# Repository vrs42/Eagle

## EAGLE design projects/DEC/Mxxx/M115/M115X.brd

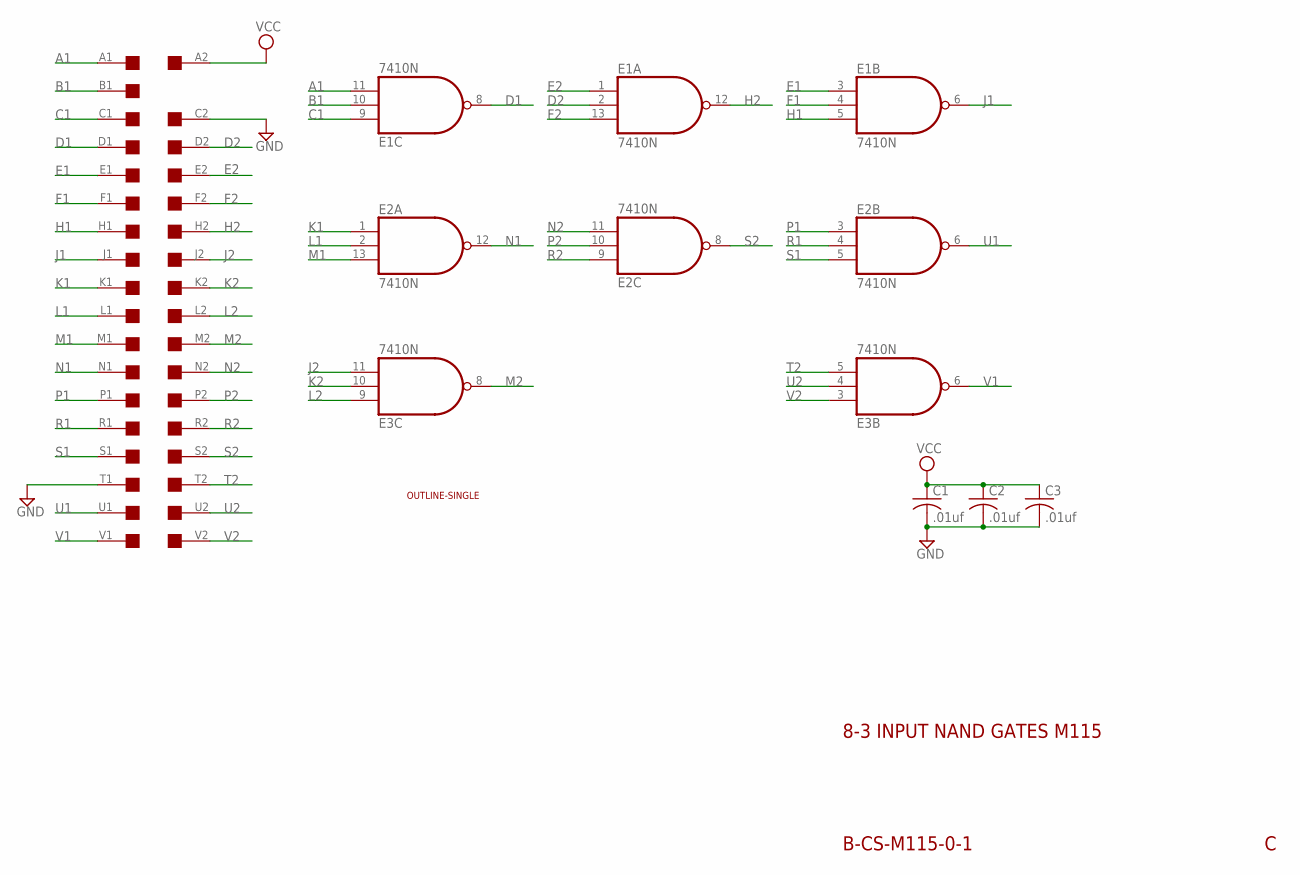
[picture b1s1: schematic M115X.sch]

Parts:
C1, C2, C3: .01uf; C050-025X075
E1, E2, E3: 7410N; DIL14
U$1: SINGLE; EDGE-CON2
U$4: OUTLINE-SINGLE; SINGLE

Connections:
A1: E1.11 (I2), U$1.A1
B1: E1.10 (I1), U$1.B1
C1: E1.9 (I0), U$1.C1
D1: E1.8 (O), U$1.D1
D2: E1.2 (I1), U$1.D2
E1: E1.3 (I0), U$1.E1
E2: E1.1 (I0), U$1.E2
F1: E1.4 (I1), U$1.F1
F2: E1.13 (I2), U$1.F2
GND: C1.2, C2.2, C3.2, E1.7 (GND), E2.7 (GND), E3.7 (GND), U$1.C2, U$1.T1
H1: E1.5 (I2), U$1.H1
H2: E1.12 (O), U$1.H2
J1: E1.6 (O), U$1.J1
J2: E3.11 (I2), U$1.J2
K1: E2.1 (I0), U$1.K1
K2: E3.10 (I1), U$1.K2
L1: E2.2 (I1), U$1.L1
L2: E3.9 (I0), U$1.L2
M1: E2.13 (I2), U$1.M1
M2: E3.8 (O), U$1.M2
N1: E2.12 (O), U$1.N1
N2: E2.11 (I2), U$1.N2
P1: E2.3 (I0), U$1.P1
P2: E2.10 (I1), U$1.P2
R1: E2.4 (I1), U$1.R1
R2: E2.9 (I0), U$1.R2
S1: E2.5 (I2), U$1.S1
S2: E2.8 (O), U$1.S2
T2: E3.5 (I2), U$1.T2
U1: E2.6 (O), U$1.U1
U2: E3.4 (I1), U$1.U2
V1: E3.6 (O), U$1.V1
V2: E3.3 (I0), U$1.V2
VCC: C1.1, C2.1, C3.1, E1.14 (VCC), E2.14 (VCC), E3.14 (VCC), U$1.A2

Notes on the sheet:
8-3 INPUT NAND GATES M115
B-CS-M115-0-1

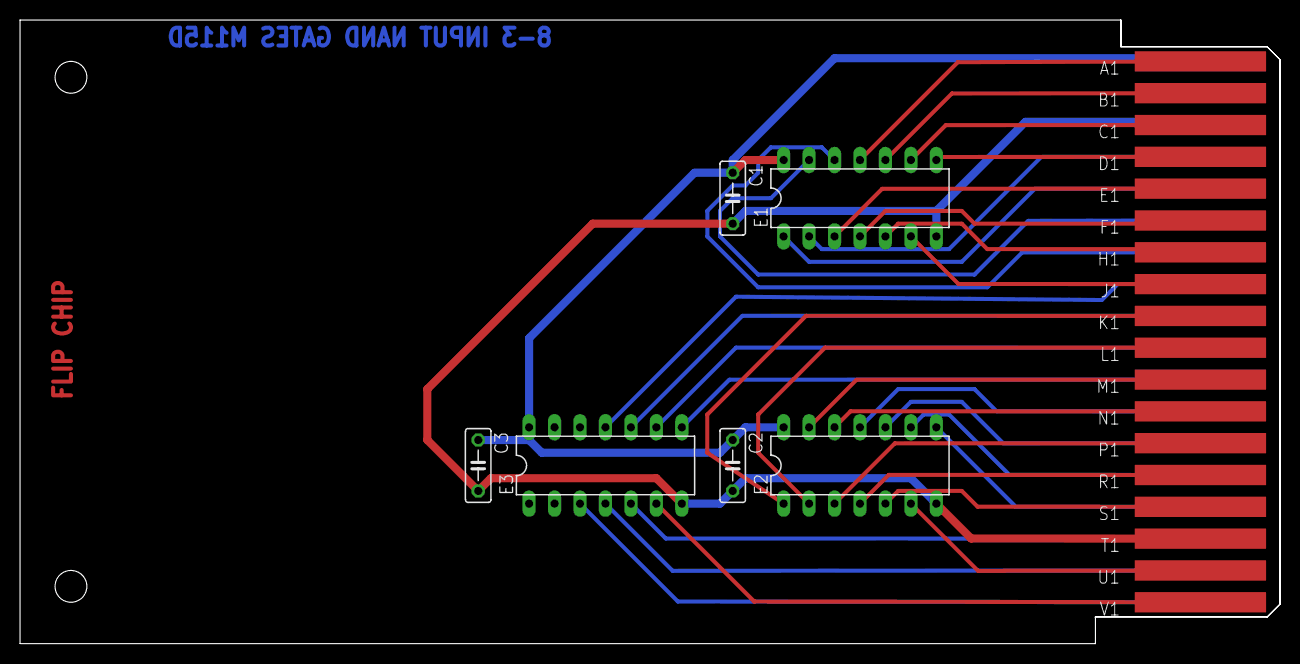
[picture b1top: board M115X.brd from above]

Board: 2 copper layers, 125.7 x 62.2 mm, 8 parts (0 on the bottom side), 34 nets.

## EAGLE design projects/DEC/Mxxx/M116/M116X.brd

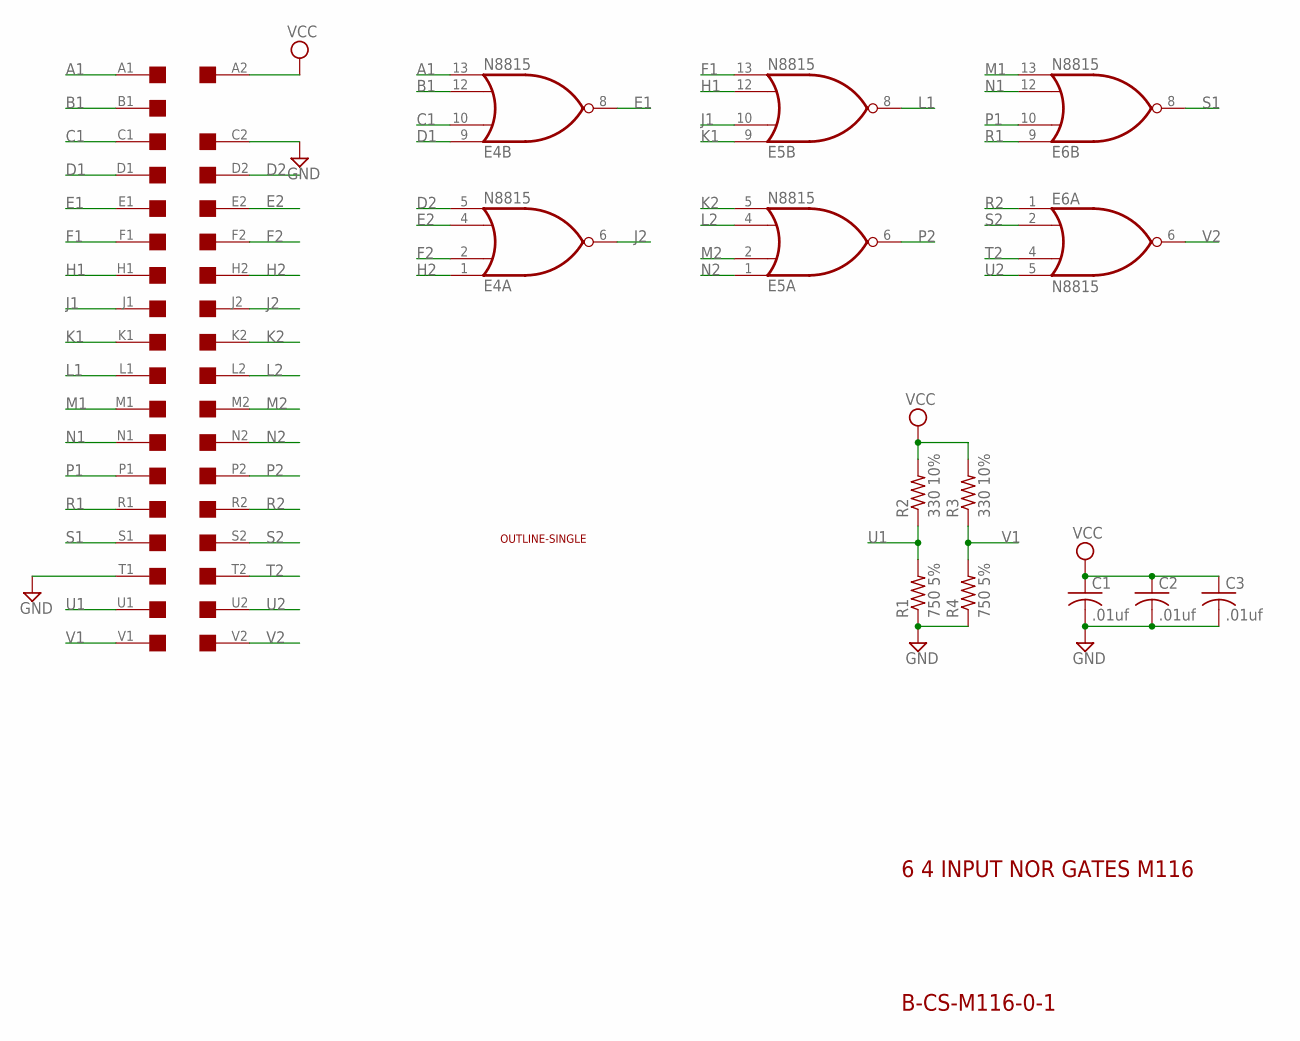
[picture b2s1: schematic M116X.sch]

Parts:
C1, C2, C3: .01uf; C050-025X075
E4, E5, E6: N8815; DIL14
R1, R4: 750 5%; 0207/10
R2, R3: 330 10%; 0207/10
U$1: SINGLE; EDGE-CON2
U$4: OUTLINE-SINGLE; SINGLE

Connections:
A1: E4.13 (I3), U$1.A1
B1: E4.12 (I2), U$1.B1
C1: E4.10 (I1), U$1.C1
D1: E4.9 (I0), U$1.D1
D2: E4.5 (I3), U$1.D2
E1: E4.8 (O), U$1.E1
E2: E4.4 (I2), U$1.E2
F1: E5.13 (I3), U$1.F1
F2: E4.2 (I1), U$1.F2
GND: C1.2, C2.2, C3.2, E4.7 (GND), E5.7 (GND), E6.7 (GND), R1.1, R4.1, U$1.C2, U$1.T1
H1: E5.12 (I2), U$1.H1
H2: E4.1 (I0), U$1.H2
J1: E5.10 (I1), U$1.J1
J2: E4.6 (O), U$1.J2
K1: E5.9 (I0), U$1.K1
K2: E5.5 (I3), U$1.K2
L1: E5.8 (O), U$1.L1
L2: E5.4 (I2), U$1.L2
M1: E6.13 (I3), U$1.M1
M2: E5.2 (I1), U$1.M2
N1: E6.12 (I2), U$1.N1
N2: E5.1 (I0), U$1.N2
P1: E6.10 (I1), U$1.P1
P2: E5.6 (O), U$1.P2
R1: E6.9 (I0), U$1.R1
R2: E6.1 (I0), U$1.R2
S1: E6.8 (O), U$1.S1
S2: E6.2 (I1), U$1.S2
T2: E6.4 (I2), U$1.T2
U1: R1.2, R2.1, U$1.U1
U2: E6.5 (I3), U$1.U2
V1: R3.1, R4.2, U$1.V1
V2: E6.6 (O), U$1.V2
VCC: C1.1, C2.1, C3.1, E4.14 (VCC), E5.14 (VCC), E6.14 (VCC), R2.2, R3.2, U$1.A2

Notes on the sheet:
6 4 INPUT NOR GATES M116
B-CS-M116-0-1

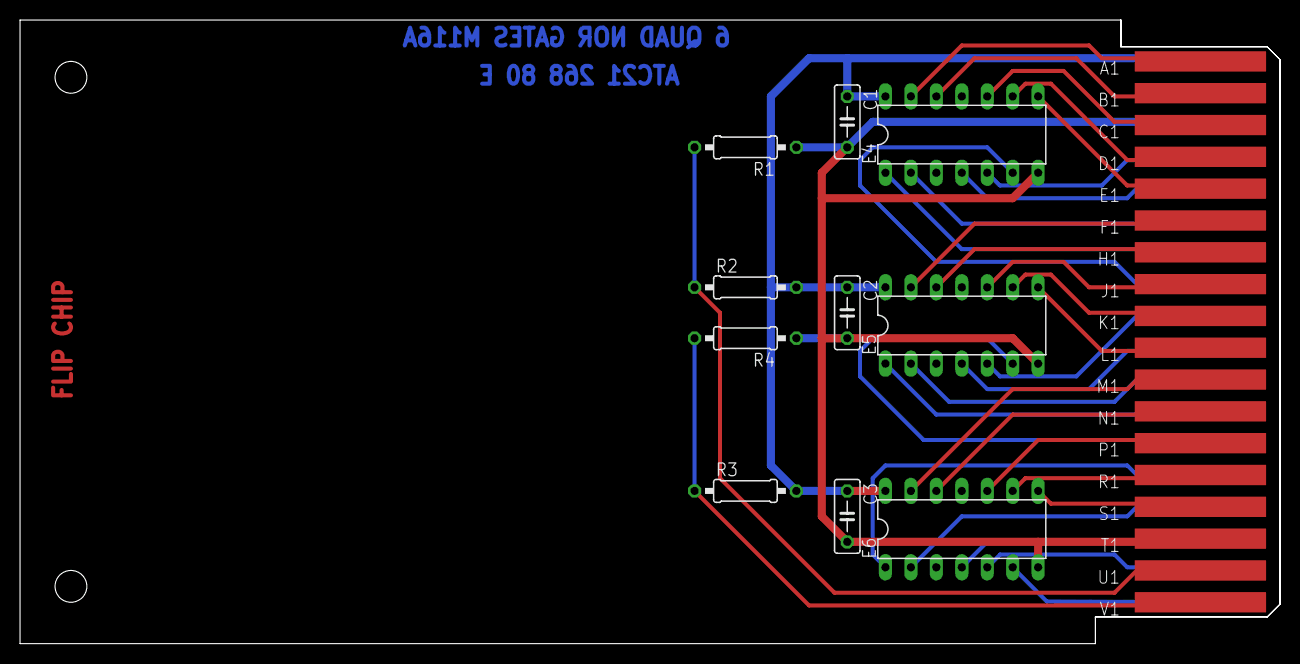
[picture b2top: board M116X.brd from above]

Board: 2 copper layers, 125.7 x 62.2 mm, 12 parts (0 on the bottom side), 34 nets.

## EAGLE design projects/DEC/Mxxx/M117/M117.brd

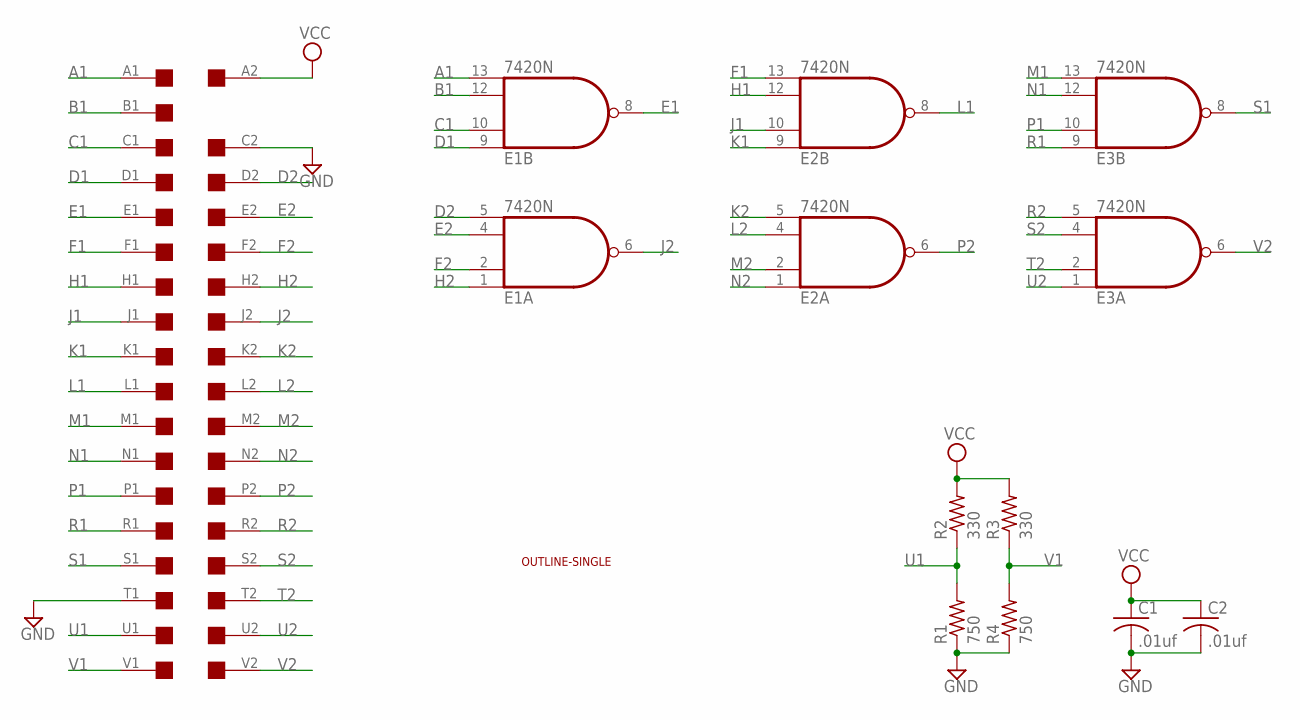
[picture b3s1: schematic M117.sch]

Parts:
C1, C2: .01uf; C050-025X075
E1, E2, E3: 7420N; DIL14
R1, R4: 750; 0207/10
R2, R3: 330; 0207/10
U$1: SINGLE; EDGE-CON2
U$4: OUTLINE-SINGLE; SINGLE

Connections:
A1: E1.13 (I3), U$1.A1
B1: E1.12 (I2), U$1.B1
C1: E1.10 (I1), U$1.C1
D1: E1.9 (I0), U$1.D1
D2: E1.5 (I3), U$1.D2
E1: E1.8 (O), U$1.E1
E2: E1.4 (I2), U$1.E2
F1: E2.13 (I3), U$1.F1
F2: E1.2 (I1), U$1.F2
GND: C1.2, C2.2, E1.7 (GND), E2.7 (GND), E3.7 (GND), R1.1, R4.1, U$1.C2, U$1.T1
H1: E2.12 (I2), U$1.H1
H2: E1.1 (I0), U$1.H2
J1: E2.10 (I1), U$1.J1
J2: E1.6 (O), U$1.J2
K1: E2.9 (I0), U$1.K1
K2: E2.5 (I3), U$1.K2
L1: E2.8 (O), U$1.L1
L2: E2.4 (I2), U$1.L2
M1: E3.13 (I3), U$1.M1
M2: E2.2 (I1), U$1.M2
N1: E3.12 (I2), U$1.N1
N2: E2.1 (I0), U$1.N2
P1: E3.10 (I1), U$1.P1
P2: E2.6 (O), U$1.P2
R1: E3.9 (I0), U$1.R1
R2: E3.5 (I3), U$1.R2
S1: E3.8 (O), U$1.S1
S2: E3.4 (I2), U$1.S2
T2: E3.2 (I1), U$1.T2
U1: R1.2, R2.1, U$1.U1
U2: E3.1 (I0), U$1.U2
V1: R3.1, R4.2, U$1.V1
V2: E3.6 (O), U$1.V2
VCC: C1.1, C2.1, E1.14 (VCC), E2.14 (VCC), E3.14 (VCC), R2.2, R3.2, U$1.A2

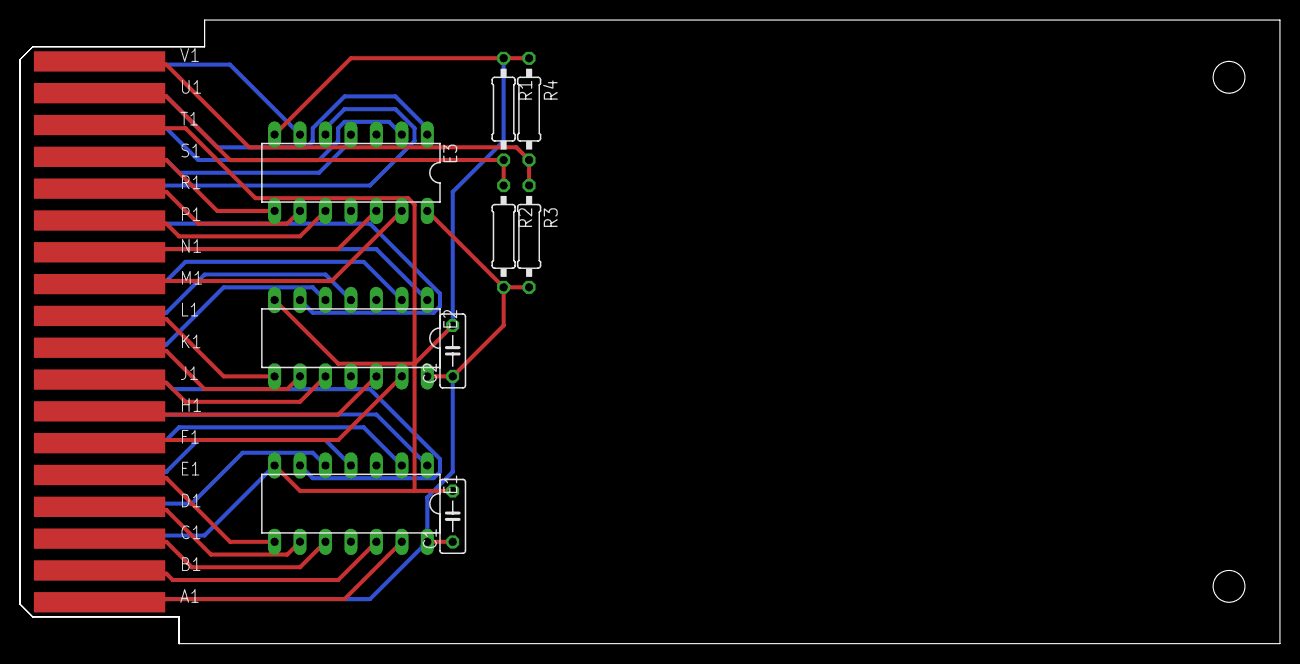
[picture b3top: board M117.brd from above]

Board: 2 copper layers, 125.7 x 62.2 mm, 11 parts (0 on the bottom side), 34 nets.

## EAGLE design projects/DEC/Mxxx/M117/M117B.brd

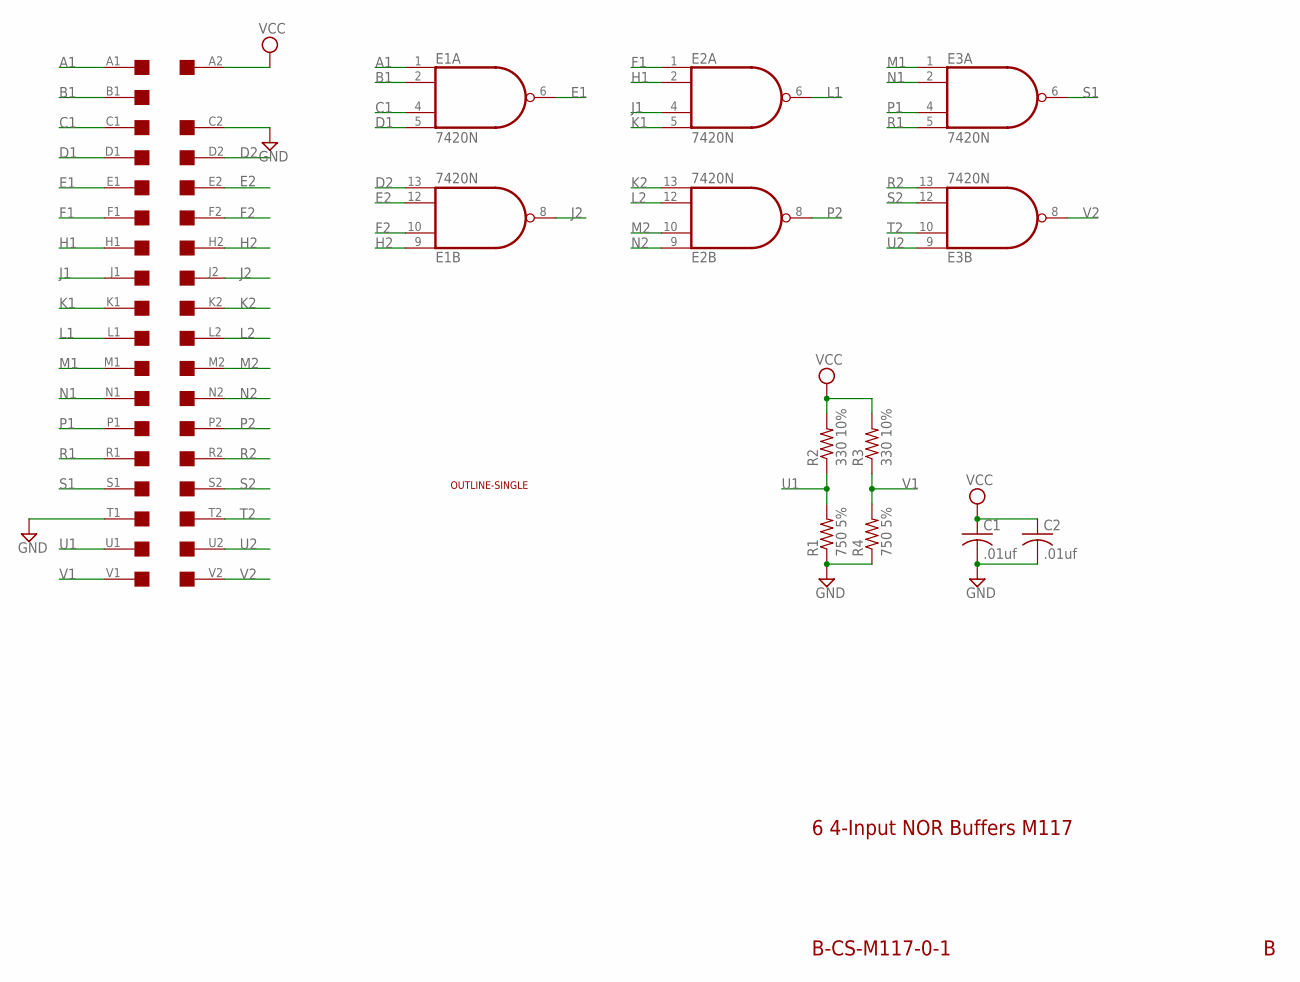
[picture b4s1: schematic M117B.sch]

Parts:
C1, C2: .01uf; C075-032X103
E1, E2, E3: 7420N; DIL14
R1, R4: 750 5%; 0207/15
R2, R3: 330 10%; 0207/15
U$1: SINGLE; EDGE-CON2
U$4: OUTLINE-SINGLE; SINGLE

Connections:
A1: E1.1 (I0), U$1.A1
B1: E1.2 (I1), U$1.B1
C1: E1.4 (I2), U$1.C1
D1: E1.5 (I3), U$1.D1
D2: E1.13 (I3), U$1.D2
E1: E1.6 (O), U$1.E1
E2: E1.12 (I2), U$1.E2
F1: E2.1 (I0), U$1.F1
F2: E1.10 (I1), U$1.F2
GND: C1.2, C2.2, E1.7 (GND), E2.7 (GND), E3.7 (GND), R1.1, R4.1, U$1.C2, U$1.T1
H1: E2.2 (I1), U$1.H1
H2: E1.9 (I0), U$1.H2
J1: E2.4 (I2), U$1.J1
J2: E1.8 (O), U$1.J2
K1: E2.5 (I3), U$1.K1
K2: E2.13 (I3), U$1.K2
L1: E2.6 (O), U$1.L1
L2: E2.12 (I2), U$1.L2
M1: E3.1 (I0), U$1.M1
M2: E2.10 (I1), U$1.M2
N1: E3.2 (I1), U$1.N1
N2: E2.9 (I0), U$1.N2
P1: E3.4 (I2), U$1.P1
P2: E2.8 (O), U$1.P2
R1: E3.5 (I3), U$1.R1
R2: E3.13 (I3), U$1.R2
S1: E3.6 (O), U$1.S1
S2: E3.12 (I2), U$1.S2
T2: E3.10 (I1), U$1.T2
U1: R1.2, R2.1, U$1.U1
U2: E3.9 (I0), U$1.U2
V1: R3.1, R4.2, U$1.V1
V2: E3.8 (O), U$1.V2
VCC: C1.1, C2.1, E1.14 (VCC), E2.14 (VCC), E3.14 (VCC), R2.2, R3.2, U$1.A2

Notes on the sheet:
6 4-Input NOR Buffers M117
B-CS-M117-0-1

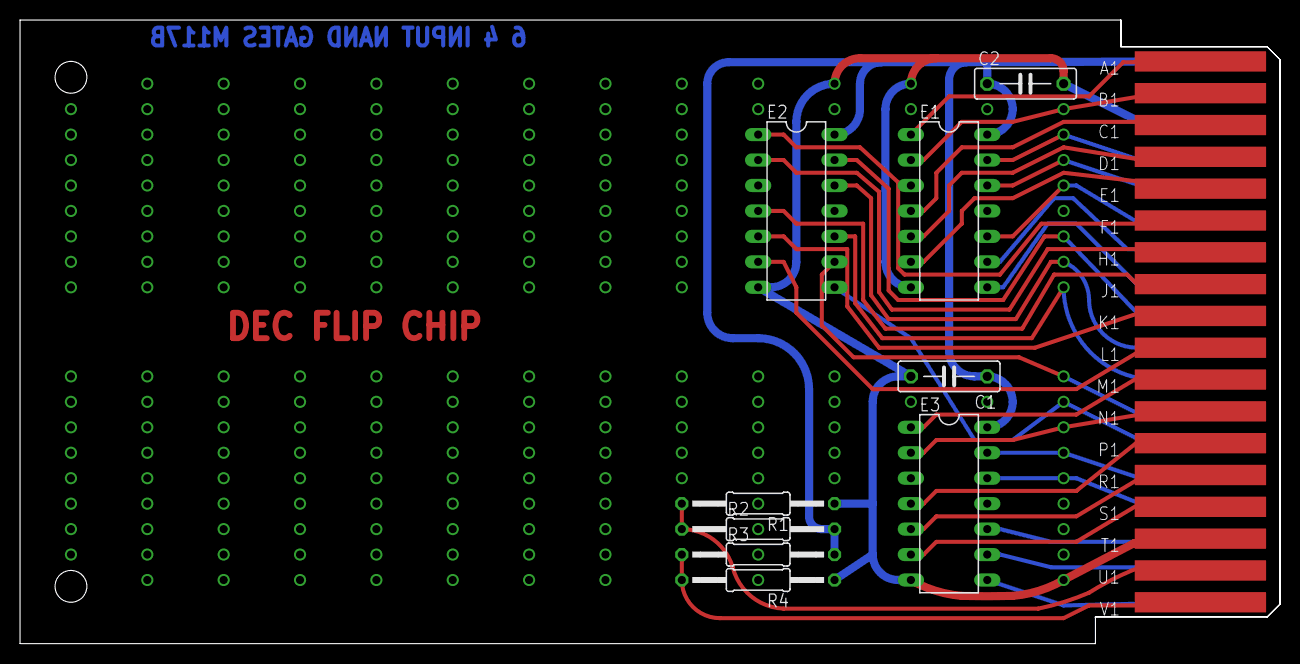
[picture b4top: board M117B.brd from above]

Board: 2 copper layers, 125.7 x 62.2 mm, 11 parts (0 on the bottom side), 34 nets.
